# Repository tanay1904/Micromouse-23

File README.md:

# Micromouse-23
The PCB built for competition aspiring to compete in Micromouse contests.

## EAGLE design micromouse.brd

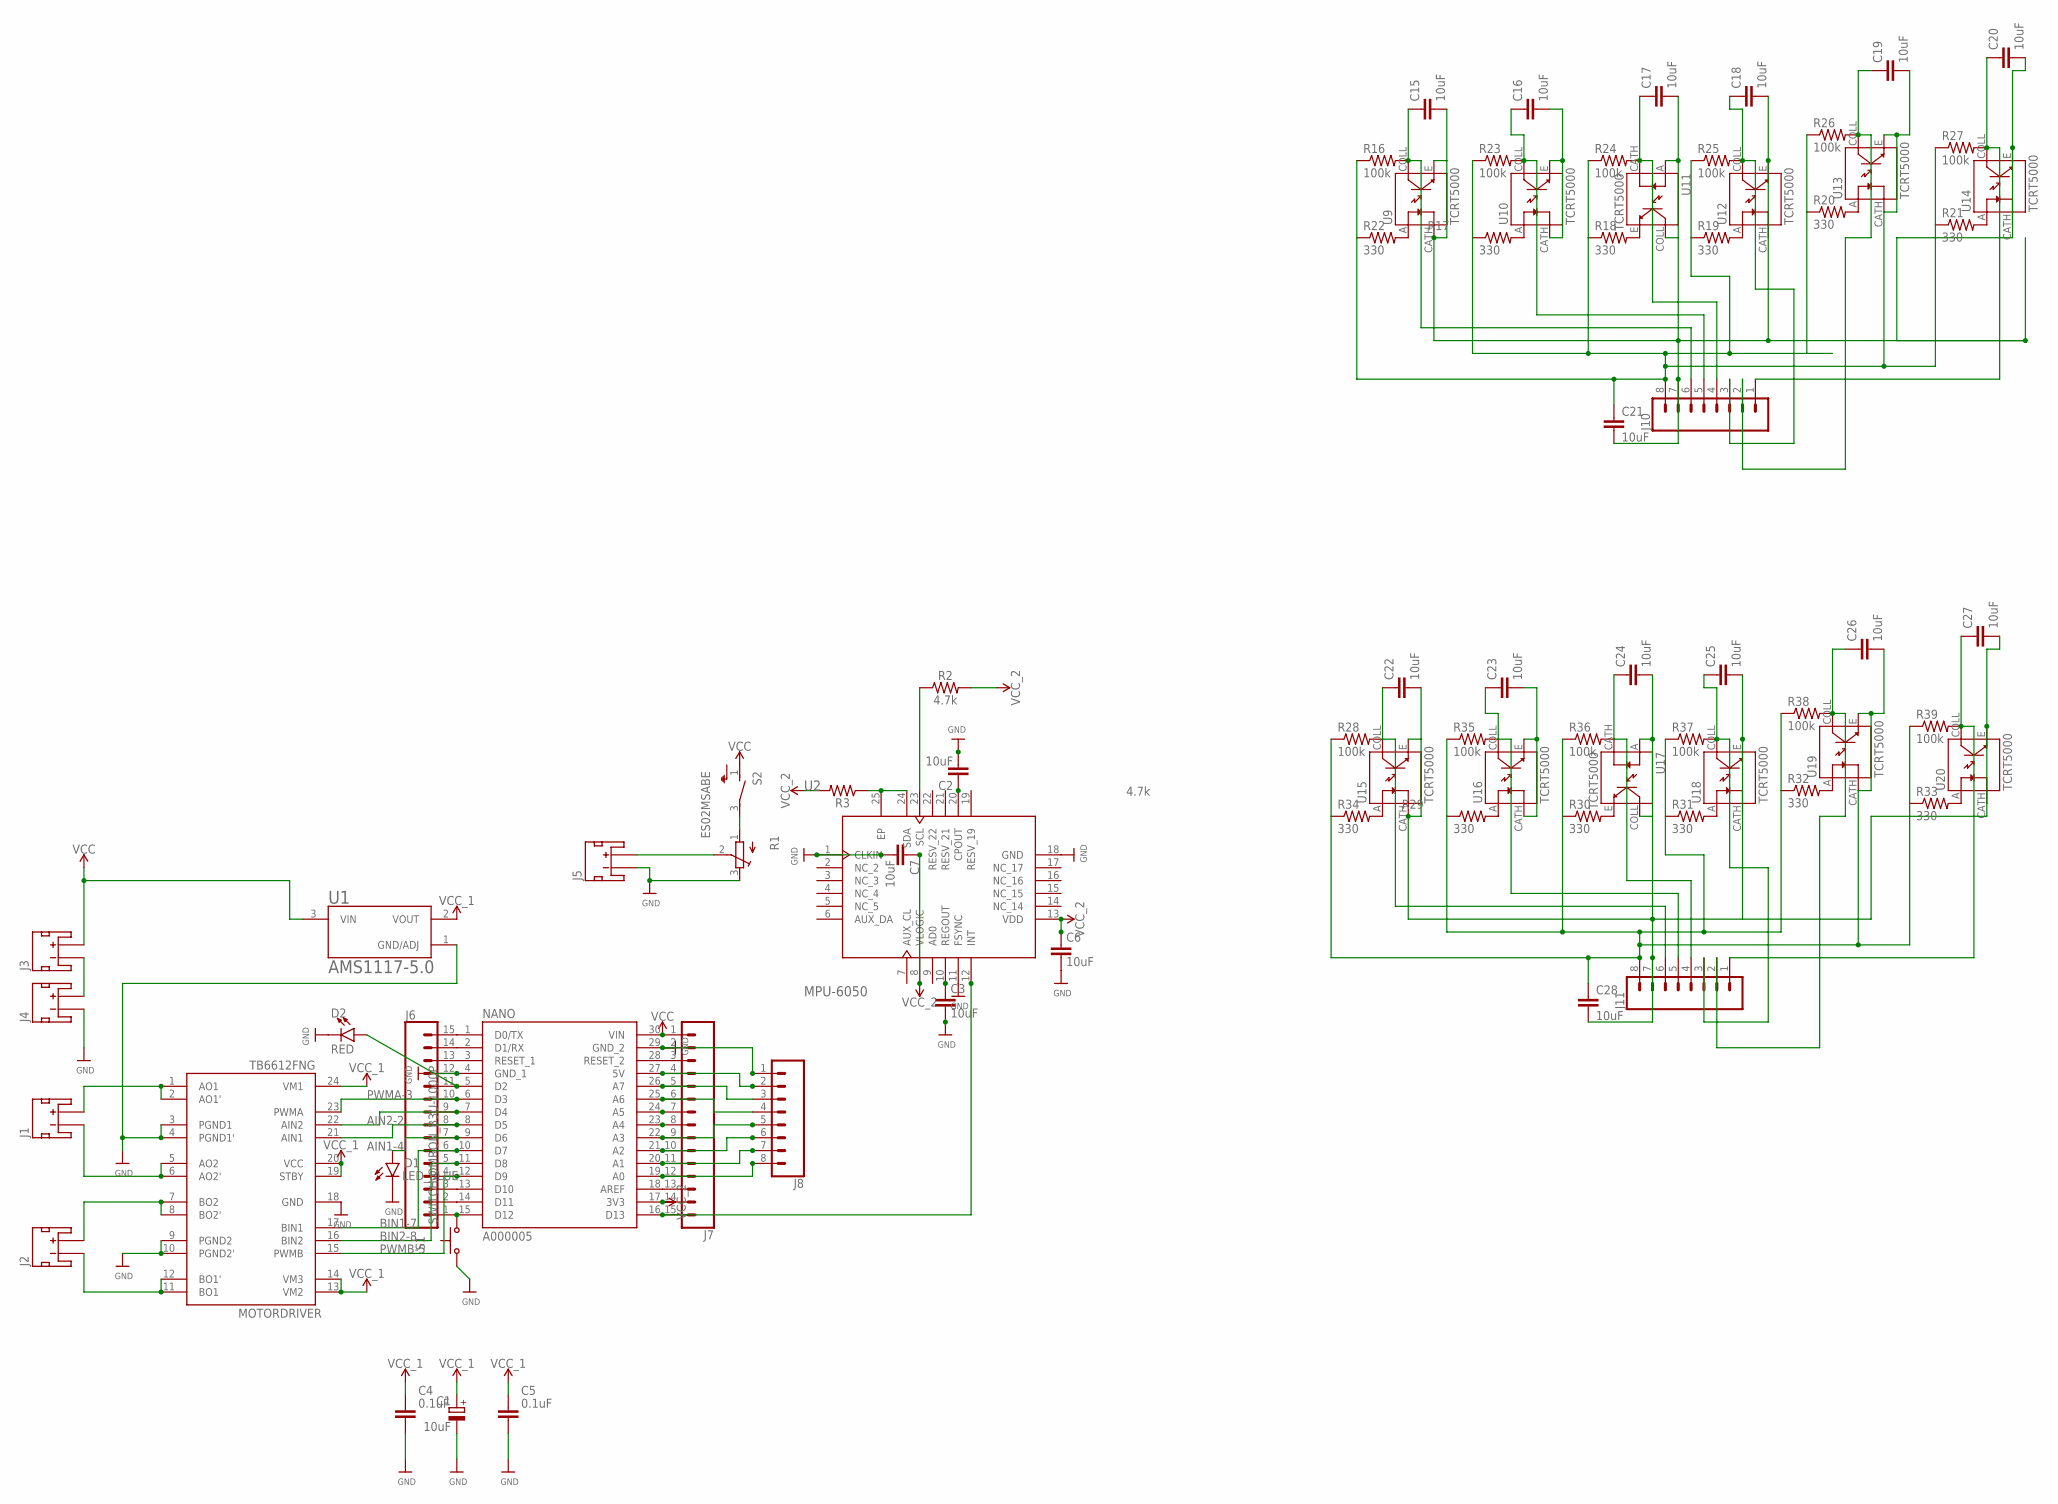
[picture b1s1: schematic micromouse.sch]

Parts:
C1: 10uF; CAPMP7343X310N
C2, C3, C6, C7: 10uF; CAP_0603
C4, C5: 0.1uF; CAPC3216X135
C15, C16, C17, C18, C19, C20, C21, C22, C23, C24, C25, C26, C27, C28: 10uF; 0603
D1: LED_BLUE; LEDC1608X39N_B
D2: RED; LED-1206
J1, J2, J3, J4, J5: JST_2MM_MALE; JST-2-SMD
J6, J7: CONN_15LOCK; 1X15_LOCK
J8, J10, J11: CONN_08NO_SILK_FEMALE_PTH; 1X08_NO_SILK
MOTORDRIVER: TB6612FNG; SSOP24
NANO: A000005; MODULE_A000005
R1: TRIM_EU-3223W; 3223W
R2, R3: 4.7k; 0603
R16, R23, R24, R26, R27, R28, R35, R36, R37, R38, R39: 100k; R0603
R17, R18, R19, R20, R21, R22, R29, R30, R31, R32, R33, R34: 330; R0603
R25: 100k; MINI_MELF-0207R
S1: SWITCH-OMRON_B3U-1000P
S2: ES02MSABE
U1: AMS1117-5.0; SOT229P700X180-4N
U2: MPU-6050; 24-VFQFN
U9, U10, U11, U12, U13, U14, U15, U16, U17, U18, U19, U20: TCRT5000; OPTO_TCRT5000

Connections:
AIN1-4: J6.8, MOTORDRIVER.21 (AIN1), NANO.8 (D5)
AIN2-2: J6.9, MOTORDRIVER.22 (AIN2), NANO.7 (D4)
BIN1-7: J6.6, MOTORDRIVER.17 (BIN1), NANO.10 (D7)
BIN2-8: J6.5, MOTORDRIVER.16 (BIN2), NANO.11 (D8)
GND: C1.2 (-), C2.2, C3.2, C4.2, C5.2, C6.2, C7.2, D1.1 (C), D2.C, J4.1 (-), J5.1 (-), J6.12, J7.2, J8.1, MOTORDRIVER.3 (PGND1), MOTORDRIVER.4 (PGND1'), MOTORDRIVER.9 (PGND2), MOTORDRIVER.10 (PGND2'), MOTORDRIVER.18 (GND), NANO.4 (GND_1), NANO.29 (GND_2), R1.3 (E), S1.1, U1.1 (GND/ADJ), U2.1 (CLKIN), U2.11 (FSYNC), U2.18 (GND)
unnamed: J1.2 (+), MOTORDRIVER.1 (AO1), MOTORDRIVER.2 (AO1')
unnamed: J7.5, J8.3, NANO.26 (A7)
unnamed: J1.1 (-), MOTORDRIVER.5 (AO2), MOTORDRIVER.6 (AO2')
unnamed: J2.2 (+), MOTORDRIVER.7 (BO2), MOTORDRIVER.8 (BO2')
unnamed: J7.4, J8.2, NANO.27 (5V)
unnamed: J2.1 (-), MOTORDRIVER.11 (BO1), MOTORDRIVER.12 (BO1')
unnamed: J7.12, J8.8, NANO.19 (A0)
unnamed: J7.11, J8.7, NANO.20 (A1)
unnamed: J7.10, J8.6, NANO.21 (A2)
unnamed: J7.9, J8.5, NANO.22 (A3)
unnamed: R3.1, U2.24 (SDA), U2.25 (EP)
unnamed: R2.1, U2.23 (SCL)
unnamed: R1.1 (A), S2.3
unnamed: D2.A, J6.11, NANO.5 (D2)
unnamed: J5.2 (+), R1.2 (S)
unnamed: J6.1, NANO.15 (D12), S1.2 (S)
unnamed: J3.1 (-), J4.2 (+)
unnamed: J6.3, NANO.13 (D10)
unnamed: D1.2 (A), J6.7, NANO.9 (D6)
unnamed: J6.13, NANO.3 (RESET_1)
unnamed: J6.14, NANO.2 (D1/RX)
unnamed: J6.15, NANO.1 (D0/TX)
unnamed: J7.3, NANO.28 (RESET_2)
unnamed: J6.2, NANO.14 (D11)
unnamed: J7.6, J8.4, NANO.25 (A6)
unnamed: J7.13, NANO.18 (AREF)
unnamed: J7.15, NANO.16 (D13), U2.12 (INT)
unnamed: J7.8, NANO.23 (A4)
unnamed: J7.7, NANO.24 (A5)
unnamed: C2.1, U2.20 (CPOUT)
unnamed: C3.1, U2.10 (REGOUT)
unnamed: C16.1, J10.5, R23.2, U10.COLL
unnamed: C17.1, J10.4, R24.2, U11.CATH
unnamed: C20.1, J10.1, R27.2, U14.COLL
unnamed: C19.1, J10.2, R26.2, U13.COLL
unnamed: C18.1, J10.3, R25.2, U12.COLL
unnamed: R22.2, U9.A
unnamed: R17.2, U10.A
unnamed: C19.2, C21.1, J10.8, R16.1, R17.1, R18.1, R19.1, R20.1, R21.1, R22.1, R23.1, R24.1, R25.1, R26.1, R27.1, U13.CATH, U13.E
unnamed: R18.2, U11.E
unnamed: C15.2, C17.2, C18.2, C20.2, C21.2, J10.7, U9.CATH, U9.E, U11.A, U11.COLL, U12.CATH, U12.E, U14.CATH, U14.E
unnamed: C16.2, U10.CATH, U10.E
unnamed: C15.1, J10.6, R16.2, U9.COLL
unnamed: R19.2, U12.A
unnamed: R20.2, U13.A
unnamed: R21.2, U14.A
unnamed: C23.1, J11.5, R35.2, U16.COLL
unnamed: C24.1, J11.4, R36.2, U17.CATH
unnamed: C27.1, J11.1, R39.2, U20.COLL
unnamed: C26.1, J11.2, R38.2, U19.COLL
unnamed: C25.1, J11.3, R37.2, U18.COLL
unnamed: R34.2, U15.A
unnamed: R29.2, U16.A
unnamed: C26.2, C28.1, J11.8, R28.1, R29.1, R30.1, R31.1, R32.1, R33.1, R34.1, R35.1, R36.1, R37.1, R38.1, R39.1, U19.CATH, U19.E
unnamed: R30.2, U17.E
unnamed: C22.2, C24.2, C25.2, C27.2, C28.2, J11.7, U15.CATH, U15.E, U17.A, U17.COLL, U18.CATH, U18.E, U20.CATH, U20.E
unnamed: C23.2, U16.CATH, U16.E
unnamed: C22.1, J11.6, R28.2, U15.COLL
unnamed: R31.2, U18.A
unnamed: R32.2, U19.A
unnamed: R33.2, U20.A
PWMA-3: J6.10, MOTORDRIVER.23 (PWMA), NANO.6 (D3)
PWMB-5: J6.4, MOTORDRIVER.15 (PWMB), NANO.12 (D9)
VCC: J3.2 (+), J7.1, NANO.30 (VIN), S2.1, U1.3 (VIN)
VCC_1: C1.1 (+), C4.1, C5.1, MOTORDRIVER.13 (VM2), MOTORDRIVER.14 (VM3), MOTORDRIVER.19 (STBY), MOTORDRIVER.20 (VCC), MOTORDRIVER.24 (VM1), U1.2 (VOUT)
VCC_2: C6.1, C7.1, J7.14, NANO.17 (3V3), R2.2, R3.2, U2.8 (VLOGIC), U2.13 (VDD)

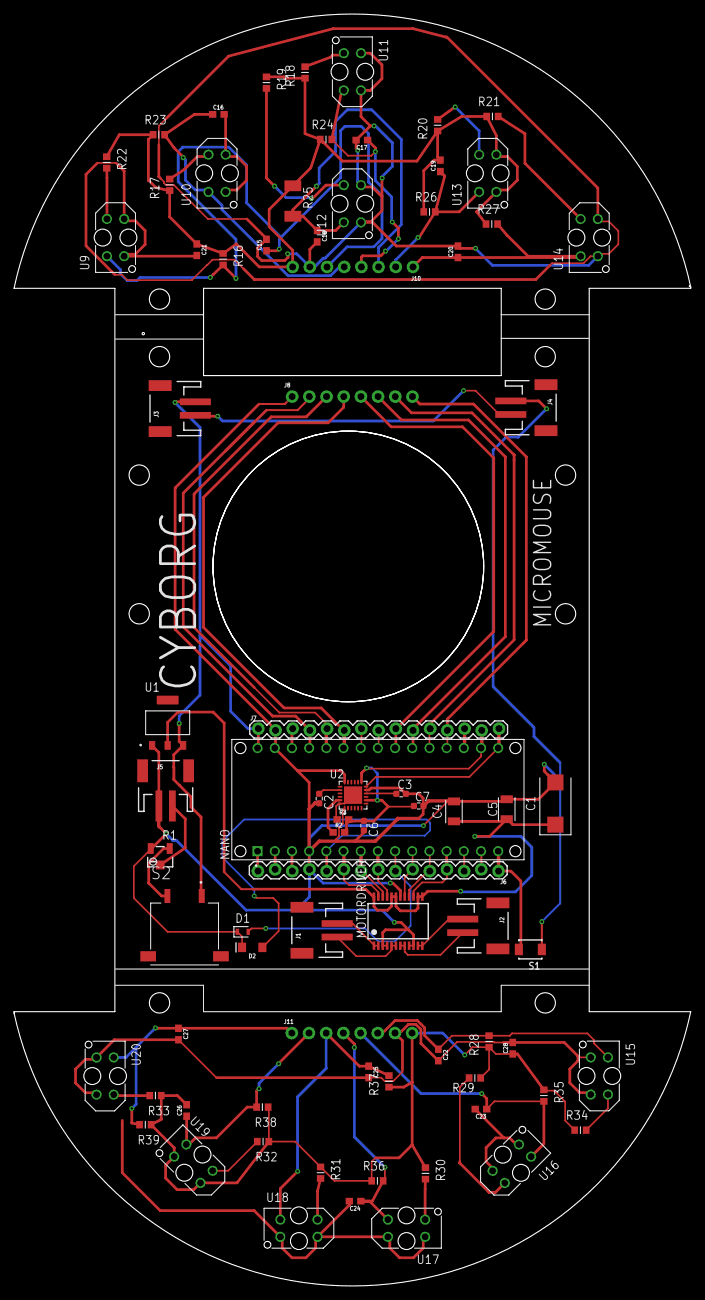
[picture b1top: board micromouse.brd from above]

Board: 2 copper layers, 100.0 x 188.0 mm, 78 parts (0 on the bottom side), 71 nets.

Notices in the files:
parts and their libraries:
SparkFun-Connectors: Licensing: Creative Commons ShareAlike 4.0 International - https://creativecommons.org/licenses/by-sa/4.0
